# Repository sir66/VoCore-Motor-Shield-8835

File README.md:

# VoCore-Motor-Shield-8835
Connection shield for using Pololu DRV8835 Dual Motor Driver Carrier and S7V7F5 Voltage Regulator with VoCore coin-size computer http://vocore.io/ https://www.pololu.com/product/2135 https://www.pololu.com/product/2119

Eagle Cad https://github.com/sparkfun/SparkFun-Eagle-Libraries/blob/master/SparkFun-Boards.lbr library is requied.

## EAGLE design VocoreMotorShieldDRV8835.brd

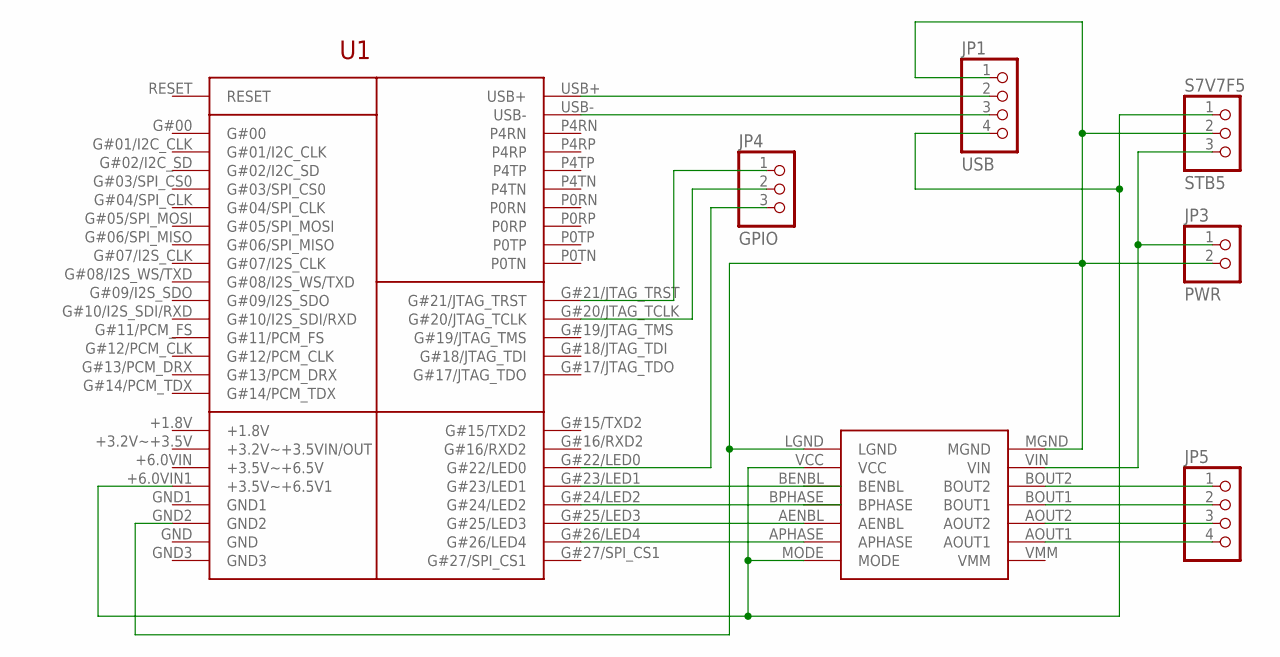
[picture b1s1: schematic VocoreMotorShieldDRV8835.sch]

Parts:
JP1: USB; 1X04
JP3: PWR; 1X02
JP4: GPIO; 1X03
JP5: PINHD-1X4; 1X04
S7V7F5: STB5; 1X03
U1: VOCORE_SHIELD; VOCORE_DOC_CUSTOM
U$1: POLOLU_MOTOR_DRV8835THROUGHHOLE; POLOLU_MOTOR_DRV_DRV8835

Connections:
unnamed: JP1.1, JP3.2, S7V7F5.2, U1.GND2, U$1.LGND, U$1.MGND
unnamed: JP3.1, S7V7F5.3, U$1.VIN
unnamed: JP1.4, S7V7F5.1, U1.+6.0VIN1 (+3.5V~+6.5V1), U$1.MODE, U$1.VCC
unnamed: U1.G#23/LED1, U$1.BENBL
unnamed: JP1.3, U1.USB-
unnamed: JP1.2, U1.USB+
unnamed: U1.G#24/LED2, U$1.BPHASE
unnamed: U1.G#25/LED3, U$1.AENBL
unnamed: U1.G#26/LED4, U$1.APHASE
unnamed: JP5.1, U$1.BOUT2
unnamed: JP5.4, U$1.AOUT1
unnamed: JP4.2, U1.G#20/JTAG_TCLK
unnamed: JP5.3, U$1.AOUT2
unnamed: JP5.2, U$1.BOUT1
unnamed: JP4.3, U1.G#22/LED0
unnamed: JP4.1, U1.G#21/JTAG_TRST

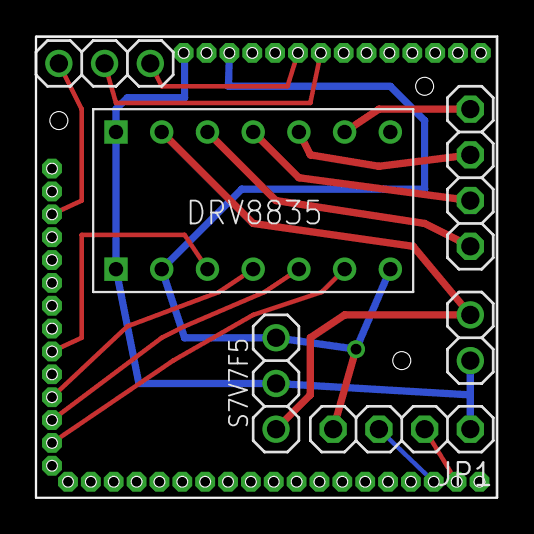
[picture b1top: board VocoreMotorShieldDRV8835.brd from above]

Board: 2 copper layers, 25.7 x 25.7 mm, 7 parts (0 on the bottom side), 16 nets.

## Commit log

2015-02-27 :lollipop: Added .gitattributes & .gitignore files
2015-02-27 Version 0.3
    Added GPIO20, GPIO21, GPIO22
2015-02-27 Add motor
    add motor demo script
